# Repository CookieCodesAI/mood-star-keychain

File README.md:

# Mood Star Keychain
A cute and aesthetic star keychain that allows you to communicate your mood to your friends!

## THIS PROJECT IS IN PROGRESS

## Features
- 4 Neopixels to allow for aesthetic lighting
- WiFi based communication with friends
- USB C port for easy power and programming

### Schematic

### PCB

### 3dmodel

### Next steps:
- Get PCB board and componenets and solder everything
- Edit firmware in accordance to the Neopixels added
- Aestheticize using pipe cleaners

### BOM
| Index                    | LCSC#     | MPN                 | Manufacturer                | Package              | Customer # | Description                                                                                 | RoHS | Quantity | MOQ | Multiple | Unit Price($) | Extended Price($) | Product Link                                       |
|--------------------------|-----------|---------------------|-----------------------------|----------------------|------------|---------------------------------------------------------------------------------------------|------|----------|-----|----------|---------------|-------------------|----------------------------------------------------|
| 1                        | C19702    | CL10A106KP8NNNC     | Samsung Electro-Mechanics   | 603                  |            | 10uF ±10% 10V Ceramic Capacitor X5R 0603                                                    | yes  | 20       | 20  | 20       | 0.0265        | 0.53              | https://www.lcsc.com/product-detail/C19702.html    |
| 2                        | C14663    | CC0603KRX7R9BB104   | YAGEO                       | 603                  |            | 100nF ±10% 50V Ceramic Capacitor X7R 0603                                                   | yes  | 100      | 100 | 100      | 0.0172        | 1.72              | https://www.lcsc.com/product-detail/C14663.html    |
| 3                        | C15849    | CL10A105KB8NNNC     | Samsung Electro-Mechanics   | 603                  |            | 1uF ±10% 50V Ceramic Capacitor X5R 0603                                                     | yes  | 50       | 50  | 50       | 0.0148        | 0.74              | https://www.lcsc.com/product-detail/C15849.html    |
| 4                        | C49256785 | ERA10V100M5X7       | JIERR                       | Through Hole,D5xL7mm |            | 100uF 10V Aluminum Electrolytic Capacitors Through Hole,D5xL7mm 2000hrs@105℃                | yes  | 20       | 20  | 20       | 0.0246        | 0.49              | https://www.lcsc.com/product-detail/C49256785.html |
| 5                        | C2761795  | WS2812B-B/T         | Worldsemi                   | SMD5050-4P           |            | SMD5050-4P LED Addressable, Specialty RoHS                                                  | yes  | 10       | 5   | 5        | 0.1072        | 1.07              | https://www.lcsc.com/product-detail/C2761795.html  |
| 6                        | C25804    | 0603WAF1002T5E      | UNI-ROYAL                   | 603                  |            | 10kΩ ±1% 100mW 0603 Thick Film Resistor                                                     | yes  | 100      | 100 | 100      | 0.0012        | 0.12              | https://www.lcsc.com/product-detail/C25804.html    |
| 7                        | C23186    | 0603WAF5101T5E      | UNI-ROYAL                   | 603                  |            | 5.1kΩ ±1% 100mW 0603 Thick Film Resistor                                                    | yes  | 100      | 100 | 100      | 0.0018        | 0.18              | https://www.lcsc.com/product-detail/C23186.html    |
| 8                        | C23138    | 0603WAF3300T5E      | UNI-ROYAL                   | 603                  |            | 330Ω ±1% 100mW 0603 Thick Film Resistor                                                     | yes  | 100      | 100 | 100      | 0.0016        | 0.16              | https://www.lcsc.com/product-detail/C23138.html    |
| 9                        | C116501   | PTS810SJM250SMTRLFS | C&K                         | SMD-4P,4.2x3.2mm     |            | Tactile Switch SPST 160gf 2.5mm J-Lead 4.2mm x 3.2mm Surface Mount                          | yes  | 8        | 1   | 1        | 0.5771        | 4.62              | https://www.lcsc.com/product-detail/C116501.html   |
| 10                       | C82899    | ESP32-WROOM-32-N4   | ESPRESSIF                   | SMD,25.5x18mm        |            | 2.4GHz ESP32-DOWDQ6 -98dBm SMD,25.5x18mm RF Transceiver Modules and Modems RoHS             | yes  | 2        | 1   | 1        | 4.3259        | 8.65              | https://www.lcsc.com/product-detail/C82899.html    |
| 11                       | C84681    | CH340C              | WCH                         | SOP-16               |            | Transceiver 2Mbps USB 2.0 SOP-16 Interface Controllers RoHS                                 | yes  | 2        | 1   | 1        | 0.5863        | 1.17              | https://www.lcsc.com/product-detail/C84681.html    |
| 12                       | C511277   | MCP1700-3302E/TO    | MICROCHIP                   | TO-92-3              |            | 3.3V Positive Fixed TO-92-3 Voltage Regulators - Linear, Low Drop Out (LDO) Regulators RoHS | yes  | 2        | 1   | 1        | 0.803         | 1.61              | https://www.lcsc.com/product-detail/C511277.html   |
| 13                       | C155176   | SN74AHCT125DR       | TI                          | SOIC-14              |            | 4.5V~5.5V 1 4 20uA 7.5ns@5V,50pF SOIC-14 Buffers, Drivers, Receivers, Transceivers RoHS     | yes  | 2        | 1   | 1        | 0.3503        | 0.7               | https://www.lcsc.com/product-detail/C155176.html   |
| 14                       | C7095263  | USB4085-GF-A        | Global Connector Technology | Through Hole         |            | USB 2.0 5A 1 -40℃~+85℃ Right Angle Through Hole USB, DVI, HDMI Connector Assemblies RoHS    | yes  | 2        | 1   | 1        | 1.4228        | 2.85              | https://www.lcsc.com/product-detail/C7095263.html  |
| 15                       |           |                     | JLCPCB                      |                      |            | PCB                                                                                         |      | 5        | 5   |          |               | $8.40             |                                                    |
|                          |           |                     |                             |                      |            |                                                                                             |      |          |     |          |               |                   |                                                    |
| TOTAL (Without Shipping) | $33.01    |                     |                             |                      |            |                                                                                             |      |          |     |          |               |                   |                                                    |
| TOTAL (With Shipping)    | $71.42    |                     |                             |                      |            |                                                                                             |      |          |     |          |               |                   |                                                    |
### Timelapses 
- [1: Starting Out](https://lapse.hackclub.com/timelapse/5bXvsicgwVzP)
- [2: Basic Firmware](https://lapse.hackclub.com/timelapse/i8mPg4Ti3nzj)
- [3: Schematic](https://lapse.hackclub.com/timelapse/T4jO5MK8scFe)
- [4: General PCB](https://lapse.hackclub.com/timelapse/qJWxwG7Hxz8r)
- [5: Finalized PCB](https://lapse.hackclub.com/timelapse/edrZpXVRfG2W)
- [6: Manufacturing](https://lapse.hackclub.com/timelapse/CAW8ewQiKnNG)

### Libraries needed
umqttsimple.py: https://raw.githubusercontent.com/RuiSantosdotme/ESP-MicroPython/master/code/MQTT/umqttsimple.py

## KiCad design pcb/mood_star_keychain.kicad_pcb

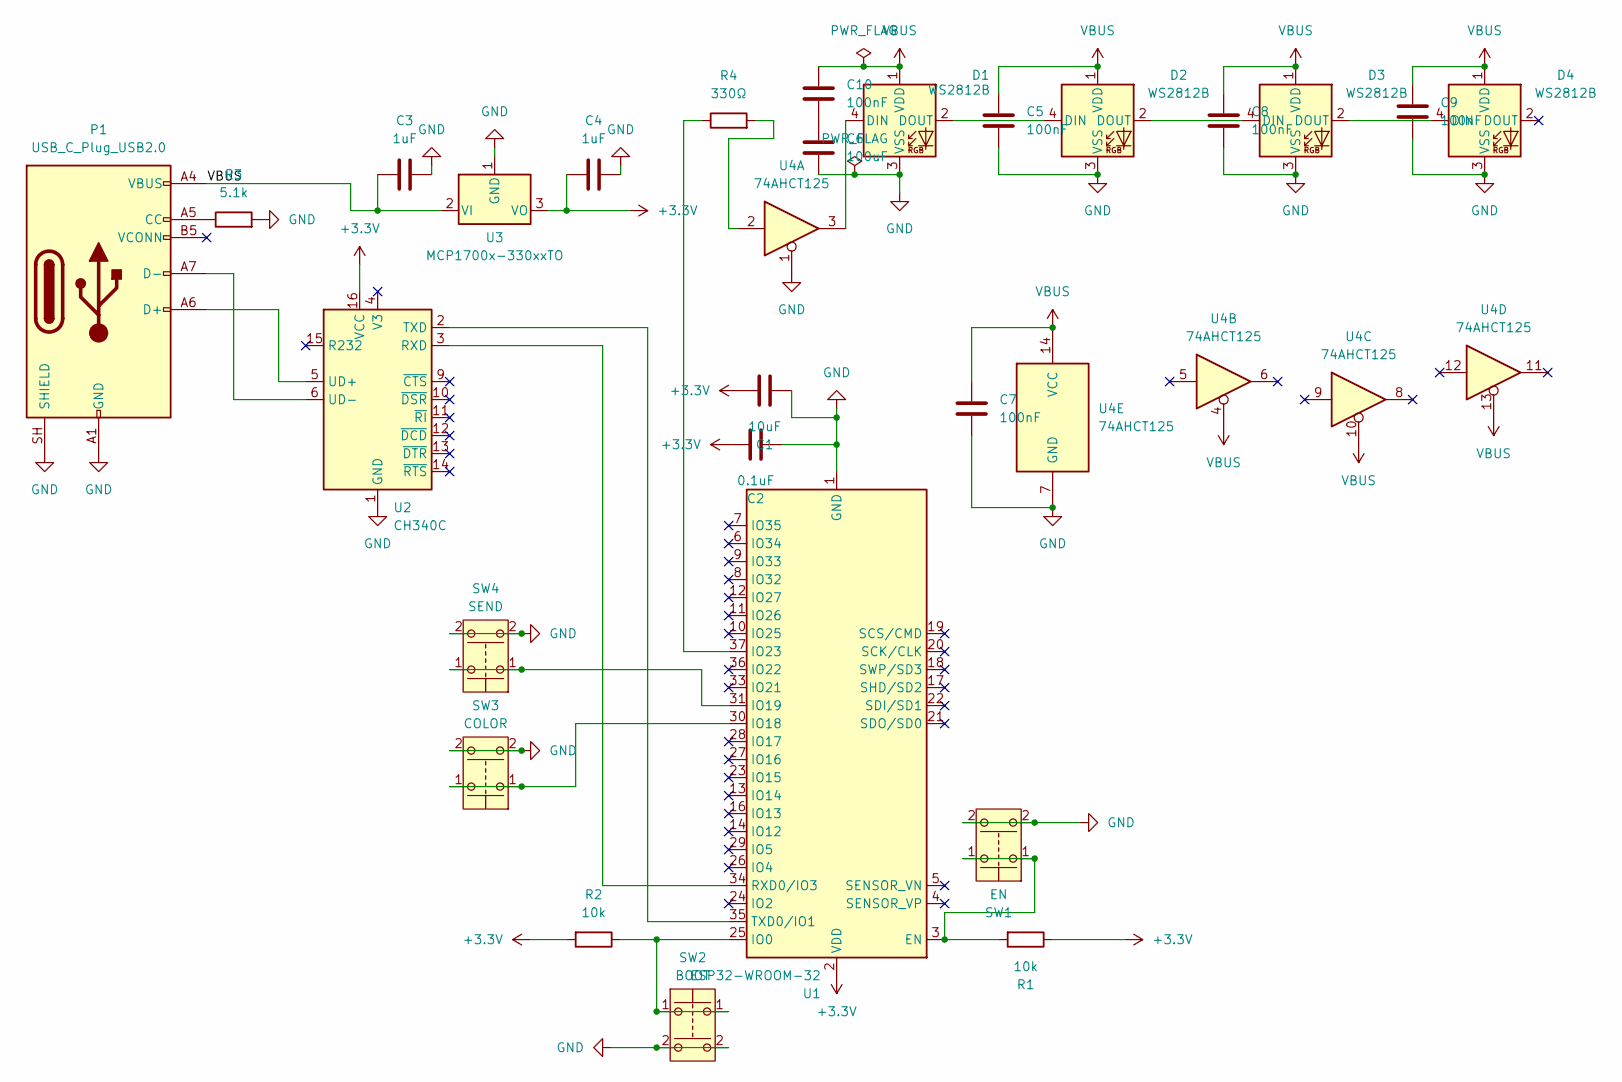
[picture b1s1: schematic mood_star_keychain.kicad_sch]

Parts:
C1: 10uF; C_0603_1608Metric
C2: 0.1uF; C_0603_1608Metric
C3, C4: 1uF; C_0603_1608Metric
C5, C7, C8, C9, C10: 100nF; C_0603_1608Metric
C6: 100uF; CP_Radial_D5.0mm_P2.00mm
D1, D2, D3, D4: WS2812B; LED_WS2812B_PLCC4_5.0x5.0mm_P3.2mm
P1: USB_C_Plug_USB2.0; USB_C_Receptacle_GCT_USB4085
R1, R2: 10k; R_0603_1608Metric
R3: 5.1k; R_0603_1608Metric
R4: 330Ω; R_0603_1608Metric
SW1: EN; SW_SPST_PTS810
SW2: BOOT; SW_SPST_PTS810
SW3: COLOR; SW_SPST_PTS810
SW4: SEND; SW_SPST_PTS810
U1: ESP32-WROOM-32
U2: CH340C; SOIC-16_3.9x9.9mm_P1.27mm
U3: MCP1700x-330xxTO; TO-92_Inline
U4: 74AHCT125; SOIC-14_3.9x8.7mm_P1.27mm

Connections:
+3.3V: C1.2, C2.2, C4.1, R1.1, R2.2, U1.2 (VDD), U2.16 (VCC), U3.3 (VO)
GND: C1.1, C2.1, C3.2, C4.2, C5.2, C6.2, C7.2, C8.2, C9.2, D1.3 (VSS), D2.3 (VSS), D3.3 (VSS), D4.3 (VSS), P1.A1 (GND), P1.A12 (GND), P1.B1 (GND), P1.B12 (GND), P1.SH (SHIELD), R3.2, SW1.2 (3), SW2.2 (3), SW3.2 (3), SW4.2 (4), U1.1 (GND), U1.15 (GND), U1.38 (GND), U1.39 (GND), U2.1 (GND), U3.1 (GND), U4.1, U4.7 (GND)
unnamed: C6.1, C10.2
unnamed: D1.4 (DIN), U4.3
unnamed: D1.2 (DOUT), D2.4 (DIN)
unnamed: D2.2 (DOUT), D3.4 (DIN)
unnamed: D3.2 (DOUT), D4.4 (DIN)
unnamed: P1.A5 (CC), R3.1
unnamed: P1.A6 (D+), U2.5 (UD+)
unnamed: P1.A7 (D-), U2.6 (UD-)
unnamed: R4.2, U4.2
unnamed: R1.2, SW1.1, U1.3 (EN)
unnamed: R2.1, SW2.1, U1.25 (IO0)
unnamed: SW3.1, U1.30 (IO18)
unnamed: SW4.1, U1.31 (IO19)
unnamed: R4.1, U1.37 (IO23)
unnamed: U1.34 (RXD0/IO3), U2.3 (RXD)
unnamed: U1.35 (TXD0/IO1), U2.2 (TXD)
VBUS: C3.1, C5.1, C7.1, C8.1, C9.1, C10.1, D1.1 (VDD), D2.1 (VDD), D3.1 (VDD), D4.1 (VDD), P1.A4 (VBUS), P1.A9 (VBUS), P1.B4 (VBUS), P1.B9 (VBUS), U3.2 (VI), U4.4, U4.10, U4.13, U4.14 (VCC)

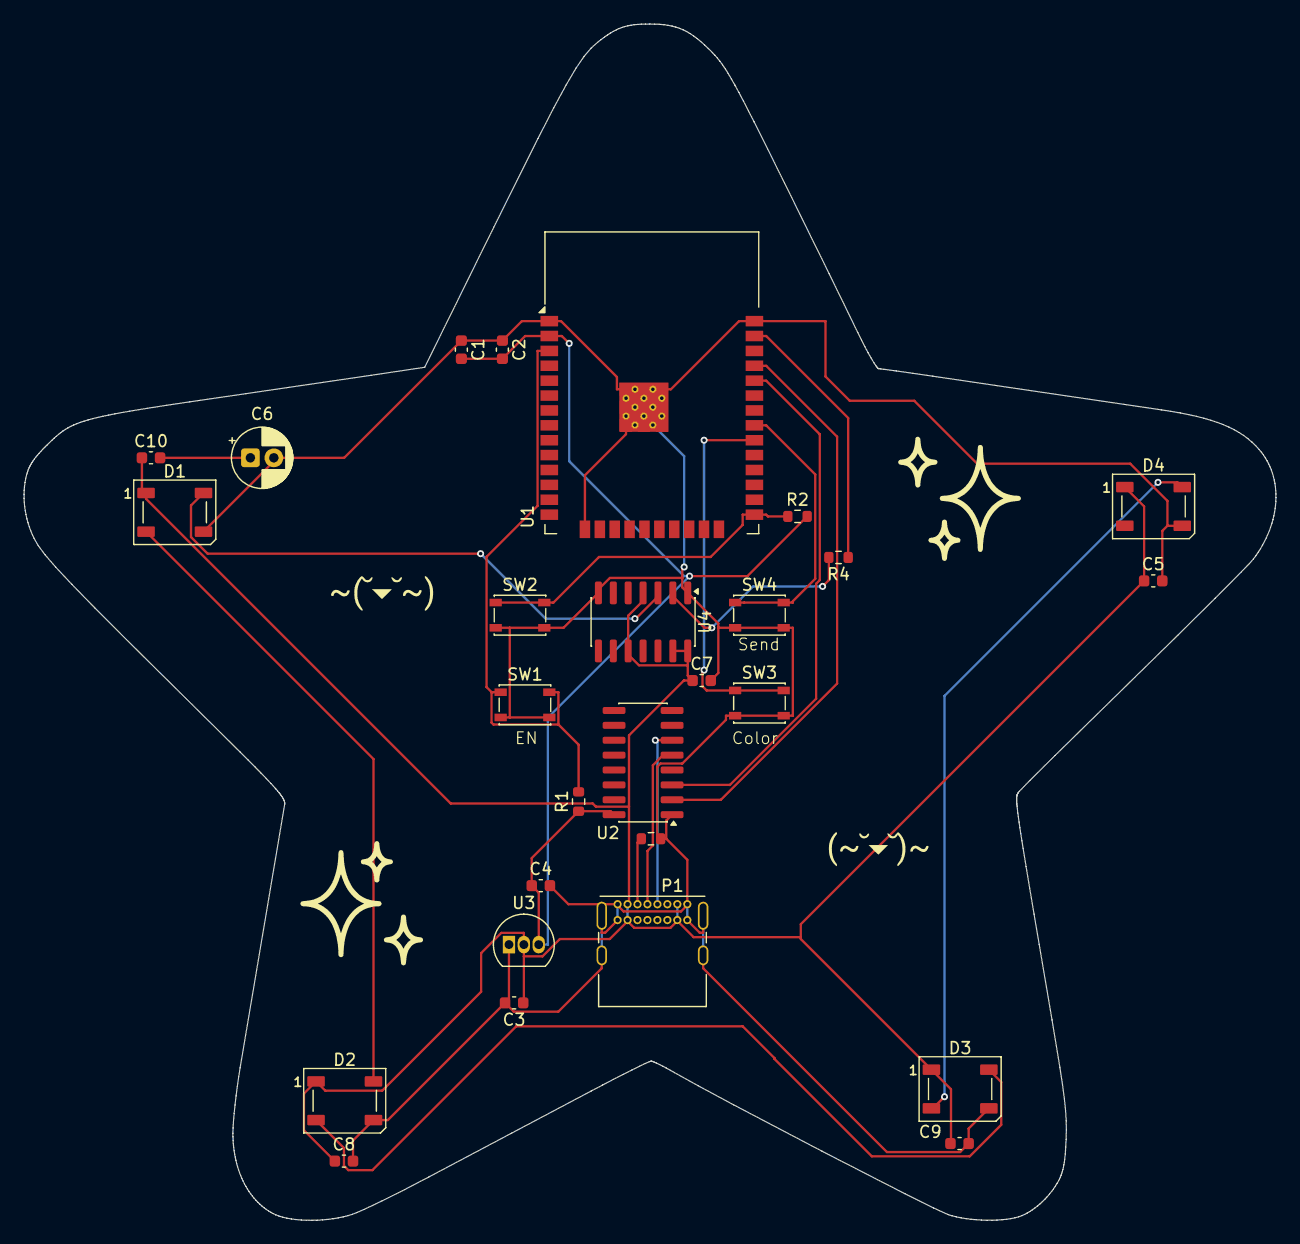
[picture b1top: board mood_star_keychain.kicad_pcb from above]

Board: 2 copper layers, 106.8 x 102.1 mm, 30 parts (0 on the bottom side), 19 nets.

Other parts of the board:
F***: LOGO
H***: LOGO
I***: LOGO

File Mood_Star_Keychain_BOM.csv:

Index,LCSC#,MPN,Manufacturer,Package,Customer #,Description,RoHS,Quantity,MOQ,Multiple,Unit Price($),Extended Price($),Product Link
1,C19702,CL10A106KP8NNNC,Samsung Electro-Mechanics,603,,10uF ±10% 10V Ceramic Capacitor X5R 0603,yes,20,20,20,0.0265,0.53,https://www.lcsc.com/product-detail/C19702.html
2,C14663,CC0603KRX7R9BB104,YAGEO,603,,100nF ±10% 50V Ceramic Capacitor X7R 0603,yes,100,100,100,0.0172,1.72,https://www.lcsc.com/product-detail/C14663.html
3,C15849,CL10A105KB8NNNC,Samsung Electro-Mechanics,603,,1uF ±10% 50V Ceramic Capacitor X5R 0603,yes,50,50,50,0.0148,0.74,https://www.lcsc.com/product-detail/C15849.html
4,C49256785,ERA10V100M5X7,JIERR,"Through Hole,D5xL7mm",,"100uF 10V Aluminum Electrolytic Capacitors Through Hole,D5xL7mm 2000hrs@105℃",yes,20,20,20,0.0246,0.49,https://www.lcsc.com/product-detail/C49256785.html
5,C2761795,WS2812B-B/T,Worldsemi,SMD5050-4P,,"SMD5050-4P LED Addressable, Specialty RoHS",yes,10,5,5,0.1072,1.07,https://www.lcsc.com/product-detail/C2761795.html
6,C25804,0603WAF1002T5E,UNI-ROYAL,603,,10kΩ ±1% 100mW 0603 Thick Film Resistor,yes,100,100,100,0.0012,0.12,https://www.lcsc.com/product-detail/C25804.html
7,C23186,0603WAF5101T5E,UNI-ROYAL,603,,5.1kΩ ±1% 100mW 0603 Thick Film Resistor,yes,100,100,100,0.0018,0.18,https://www.lcsc.com/product-detail/C23186.html
8,C23138,0603WAF3300T5E,UNI-ROYAL,603,,330Ω ±1% 100mW 0603 Thick Film Resistor,yes,100,100,100,0.0016,0.16,https://www.lcsc.com/product-detail/C23138.html
9,C116501,PTS810SJM250SMTRLFS,C&K,"SMD-4P,4.2x3.2mm",,Tactile Switch SPST 160gf 2.5mm J-Lead 4.2mm x 3.2mm Surface Mount,yes,8,1,1,0.5771,4.62,https://www.lcsc.com/product-detail/C116501.html
10,C82899,ESP32-WROOM-32-N4,ESPRESSIF,"SMD,25.5x18mm",,"2.4GHz ESP32-DOWDQ6 -98dBm SMD,25.5x18mm RF Transceiver Modules and Modems RoHS",yes,2,1,1,4.3259,8.65,https://www.lcsc.com/product-detail/C82899.html
11,C84681,CH340C,WCH,SOP-16,,Transceiver 2Mbps USB 2.0 SOP-16 Interface Controllers RoHS,yes,2,1,1,0.5863,1.17,https://www.lcsc.com/product-detail/C84681.html
12,C511277,MCP1700-3302E/TO,MICROCHIP,TO-92-3,,"3.3V Positive Fixed TO-92-3 Voltage Regulators - Linear, Low Drop Out (LDO) Regulators RoHS",yes,2,1,1,0.803,1.61,https://www.lcsc.com/product-detail/C511277.html
13,C155176,SN74AHCT125DR,TI,SOIC-14,,"4.5V~5.5V 1 4 20uA 7.5ns@5V,50pF SOIC-14 Buffers, Drivers, Receivers, Transceivers RoHS",yes,2,1,1,0.3503,0.7,https://www.lcsc.com/product-detail/C155176.html
14,C7095263,USB4085-GF-A,Global Connector Technology,Through Hole,,"USB 2.0 5A 1 -40℃~+85℃ Right Angle Through Hole USB, DVI, HDMI Connector Assemblies RoHS",yes,2,1,1,1.4228,2.85,https://www.lcsc.com/product-detail/C7095263.html
15,,,JLCPCB,,,PCB,,5,5,,,$8.40,
,,,,,,,,,,,,,
TOTAL (Without Shipping),$33.01,,,,,,,,,,,,
TOTAL (With Shipping),$71.42,,,,,,,,,,,,

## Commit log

2026-06-15 created readme and basic main.py color switch code
2026-06-16 finished basic firmware and esp32s are communicating properly
2026-06-17 added all kicad files and manufacturing files as well as bom
2026-06-18 finished README
2026-06-18 added step files
